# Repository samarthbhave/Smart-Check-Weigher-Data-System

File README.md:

# Smart-Check-Weigher-Data-System
Its My final year project which works and has been implemented in the industry.
The steps to proceed are given inside the Smart-Check-Weigher-Data-System branch

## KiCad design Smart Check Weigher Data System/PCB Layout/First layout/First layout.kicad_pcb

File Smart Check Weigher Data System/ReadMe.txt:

Steps to Execute the project :-
1) Go through the "Blackbook_Final.pdf" file and the Presentation in the Project Demo folder to get an overall idea on how to successfully run the project.
2) Go through the sample.py python file for the Desktop representation of the project.
3) Use the Rookie and Rookie_2 code to et the same output of step 2, but on Arduino IDE.
4) Use the Final_Code folder to get the final working code with google sheet enabled.
5) Refer the videos in the Project Demo folder to get the result outputs.
6) Use the .aia file to get a clear idea on the working of the android app. (http://appinventor.mit.edu/)
7) Or alternatively use the android app given to directly get the output of the current sheet.

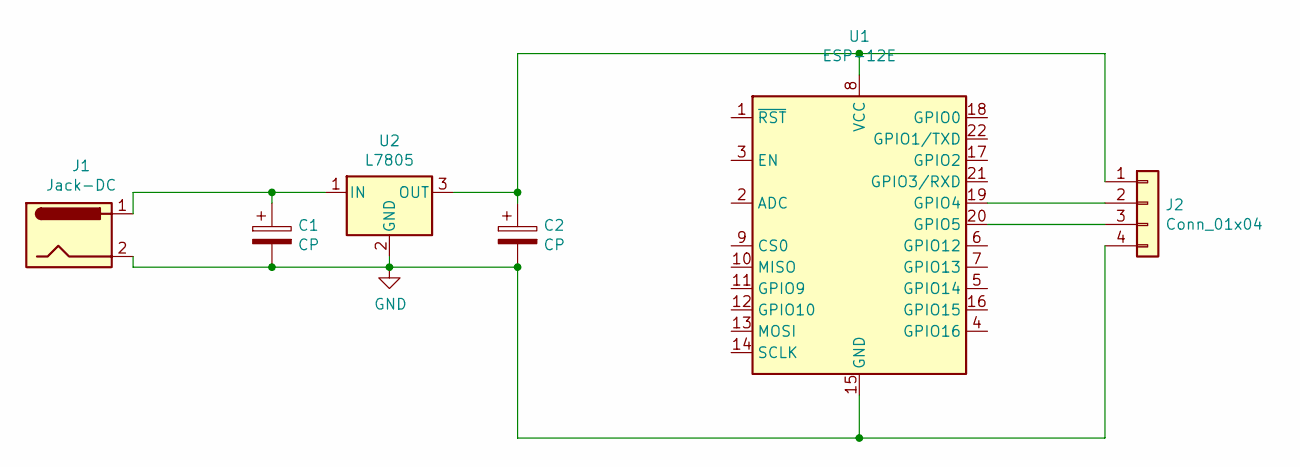
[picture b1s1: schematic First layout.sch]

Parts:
C1, C2: CP; CP_Radial_D4.0mm_P1.50mm
J1: Jack-DC; BarrelJack_Horizontal
J2: Conn_01x04; PinHeader_1x04_P1.00mm_Vertical
U1: ESP-12E
U2: L7805; PinHeader_1x03_P1.00mm_Vertical

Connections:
GND: C1.2, C2.2, J1.2, J2.4, U1.15 (GND), U2.2 (GND)
unnamed: C1.1, J1.1, U2.1 (IN)
unnamed: C2.1, J2.1, U1.8 (VCC), U2.3 (OUT)
unnamed: J2.2, U1.19 (GPIO4)
unnamed: J2.3, U1.20 (GPIO5)

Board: 2 copper layers, 6 parts (0 on the bottom side), 5 nets, no tracks yet.
